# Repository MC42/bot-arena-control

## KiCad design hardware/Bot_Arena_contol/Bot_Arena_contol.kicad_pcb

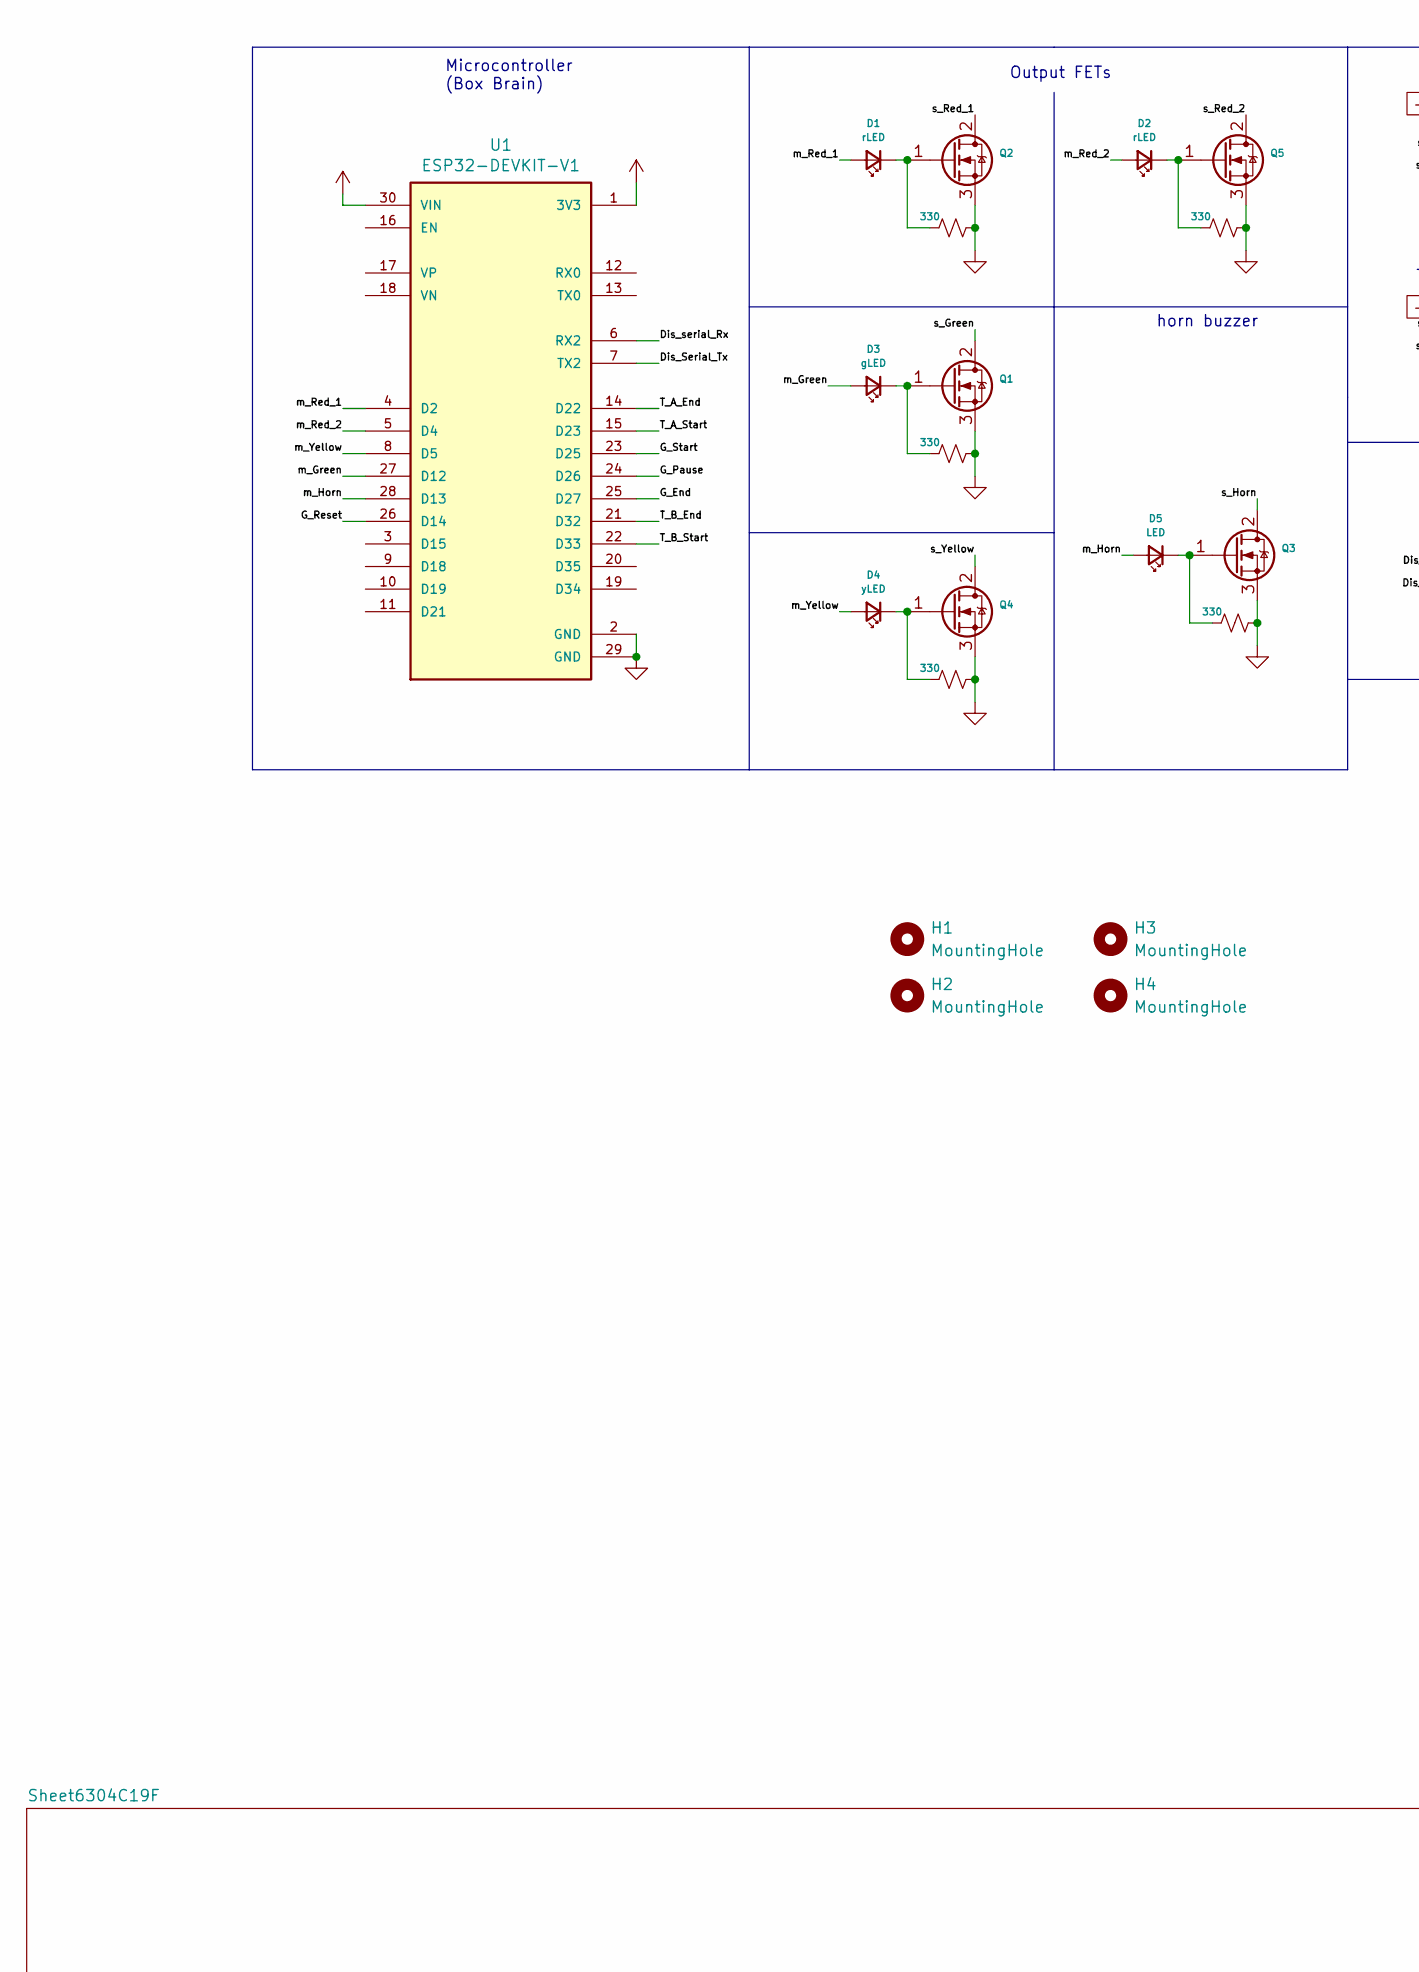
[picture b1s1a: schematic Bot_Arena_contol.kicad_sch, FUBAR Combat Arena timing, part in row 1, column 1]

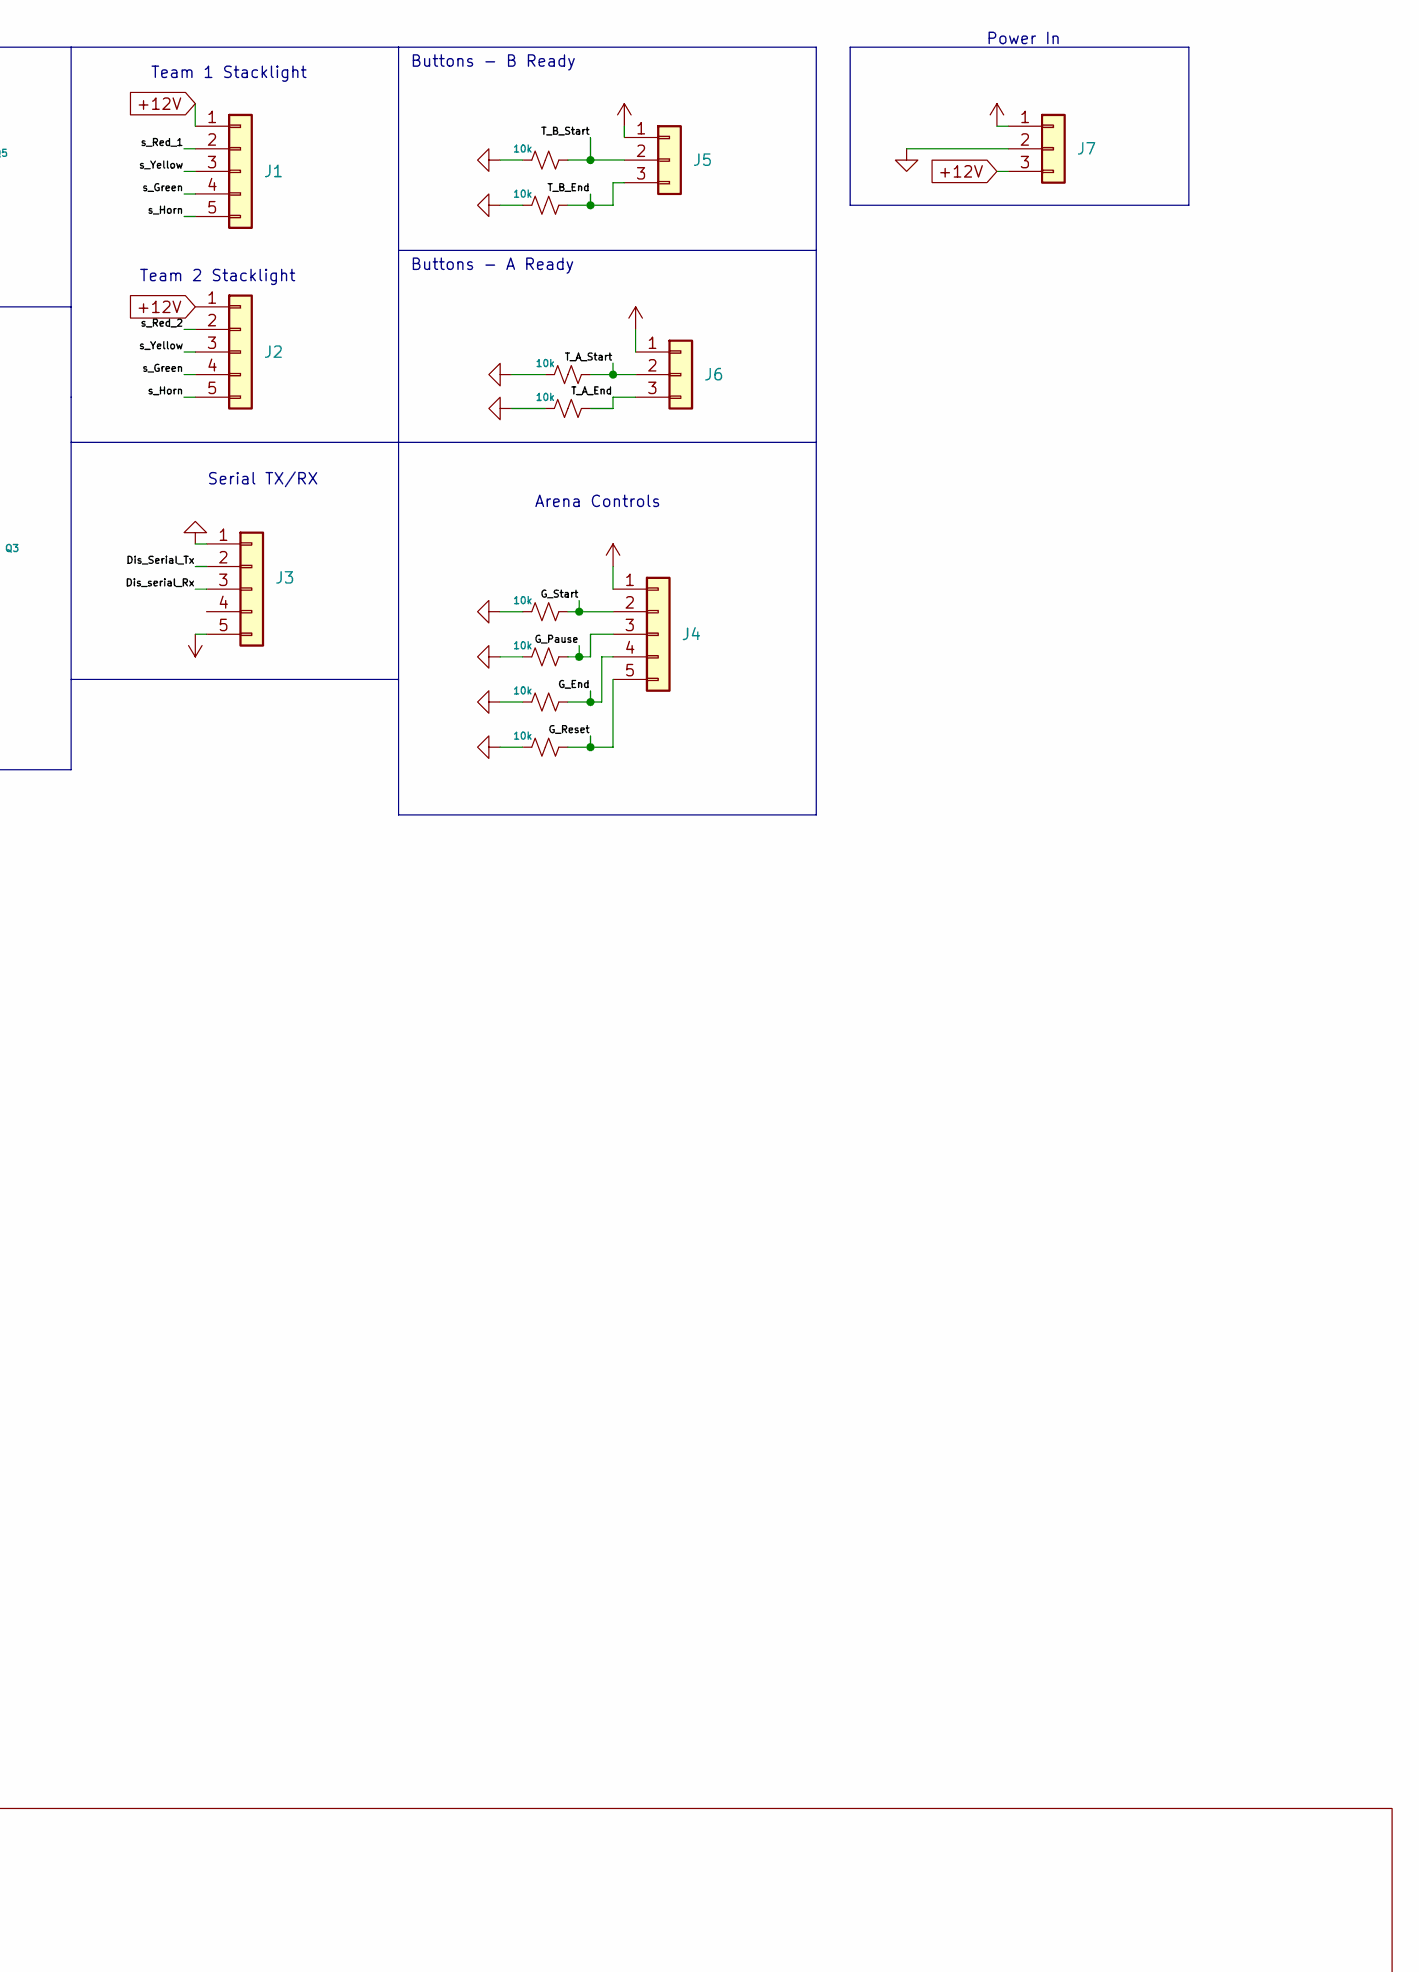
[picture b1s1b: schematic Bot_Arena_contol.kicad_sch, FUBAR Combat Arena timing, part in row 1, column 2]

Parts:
D1, D2: rLED; R_Axial_DIN0411_L9.9mm_D3.6mm_P7.62mm_Vertical
D3: gLED; R_Axial_DIN0411_L9.9mm_D3.6mm_P7.62mm_Vertical
D4: yLED; R_Axial_DIN0411_L9.9mm_D3.6mm_P7.62mm_Vertical
D5: LED; R_Axial_DIN0411_L9.9mm_D3.6mm_P7.62mm_Vertical
H1, H2, H3, H4: MountingHole; MountingHole_3.2mm_M3
J1, J2, J3, J4: 5Pin_5mm_plus_2.54_pin; 5pin_5mmpitch_plus_2.54_combo
J5, J6, J7: 3Pin_5mm_plus_2.54_pin; 3pin_5mmpitch_plus_2.54mm
Q1, Q2, Q3, Q4, Q5: (no value)
R1, R7, R8, R9, R10, R11, R12, R13: 10k; R_Axial_DIN0207_L6.3mm_D2.5mm_P10.16mm_Horizontal
R2, R3, R4, R5, R6: 330; R_Axial_DIN0207_L6.3mm_D2.5mm_P10.16mm_Horizontal
U1: ESP32-DEVKIT-V1; MODULE_ESP32_DEVKIT_V1; PARTREV N/A

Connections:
+12V: J1.1, J2.1, J7.3
/Dis_Serial_Tx: J3.2, U1.7 (TX2)
/Dis_serial_Rx: J3.3, U1.6 (RX2)
/G_End: J4.4, R12.1, U1.25 (D27)
/G_Pause: J4.3, R11.1, U1.24 (D26)
/G_Reset: J4.5, R13.1, U1.26 (D14)
/G_Start: J4.2, R10.1, U1.23 (D25)
/T_A_End: J6.3, R9.1, U1.14 (D22)
/T_A_Start: J6.2, R8.1, U1.15 (D23)
/T_B_End: J5.3, R7.1, U1.21 (D32)
/T_B_Start: J5.2, R1.1, U1.22 (D33)
/m_Green: D3.2 (A), U1.27 (D12)
/m_Horn: D5.2 (A), U1.28 (D13)
/m_Red_1: D1.2 (A), U1.4 (D2)
/m_Red_2: D2.2 (A), U1.5 (D4)
/m_Yellow: D4.2 (A), U1.8 (D5)
/s_Green: J1.4, J2.4, Q1.2 (D)
/s_Horn: J1.5, J2.5, Q3.2 (D)
/s_Red_1: J1.2, Q2.2 (D)
/s_Red_2: J2.2, Q5.2 (D)
/s_Yellow: J1.3, J2.3, Q4.2 (D)
unnamed: D1.1 (K), Q2.1 (G), R3.2
unnamed: D2.1 (K), Q5.1 (G), R6.2
unnamed: D3.1 (K), Q1.1 (G), R2.2
unnamed: D4.1 (K), Q4.1 (G), R5.2
unnamed: D5.1 (K), Q3.1 (G), R4.2

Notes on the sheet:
Arena Controls
Microcontroller (Box Brain)
Buttons - A Ready
Team 2 Stacklight
Power In
Serial TX/RX
Team 1 Stacklight
Output FETs
horn buzzer
Buttons - B Ready

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
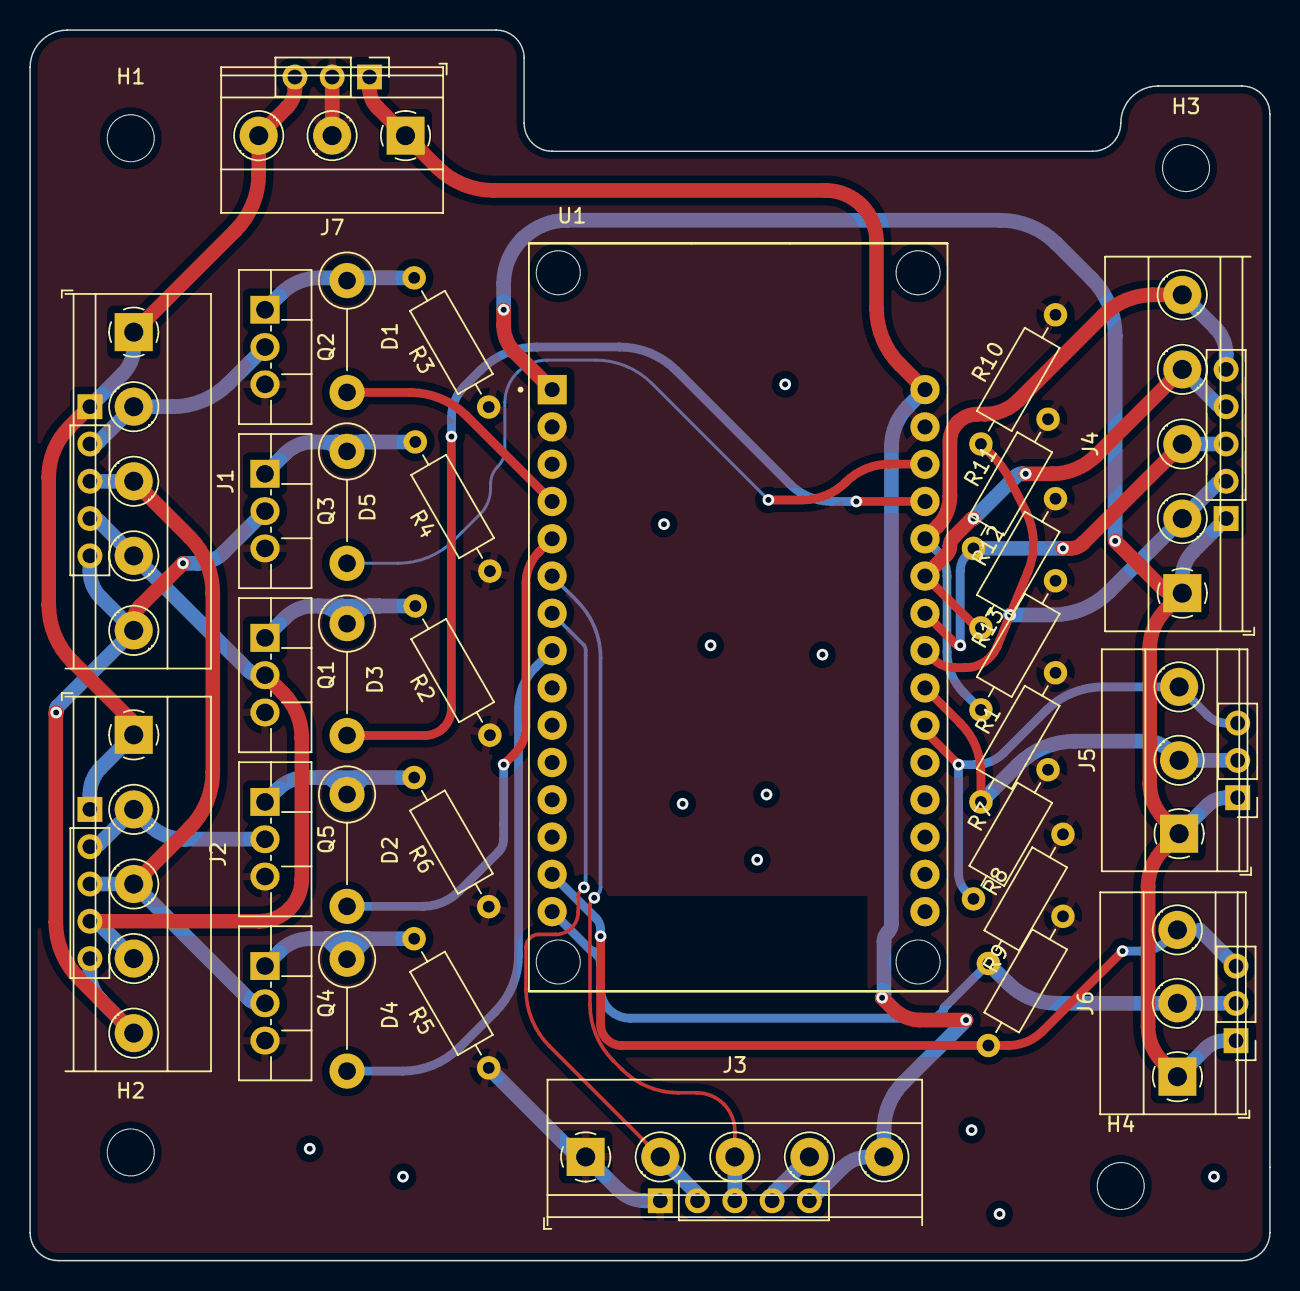
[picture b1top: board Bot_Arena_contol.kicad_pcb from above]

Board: 2 copper layers, 84.5 x 83.8 mm, 35 parts (0 on the bottom side), 29 nets.

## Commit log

2022-08-24 Added initial pass of schematic cleanup.
2022-08-24 Add footprint cleanup.
2022-08-24 Added cleaned up outline for now. Still failing DRC, so we're not going to touch that atm.
2022-08-24 Added pretty PCB version.
